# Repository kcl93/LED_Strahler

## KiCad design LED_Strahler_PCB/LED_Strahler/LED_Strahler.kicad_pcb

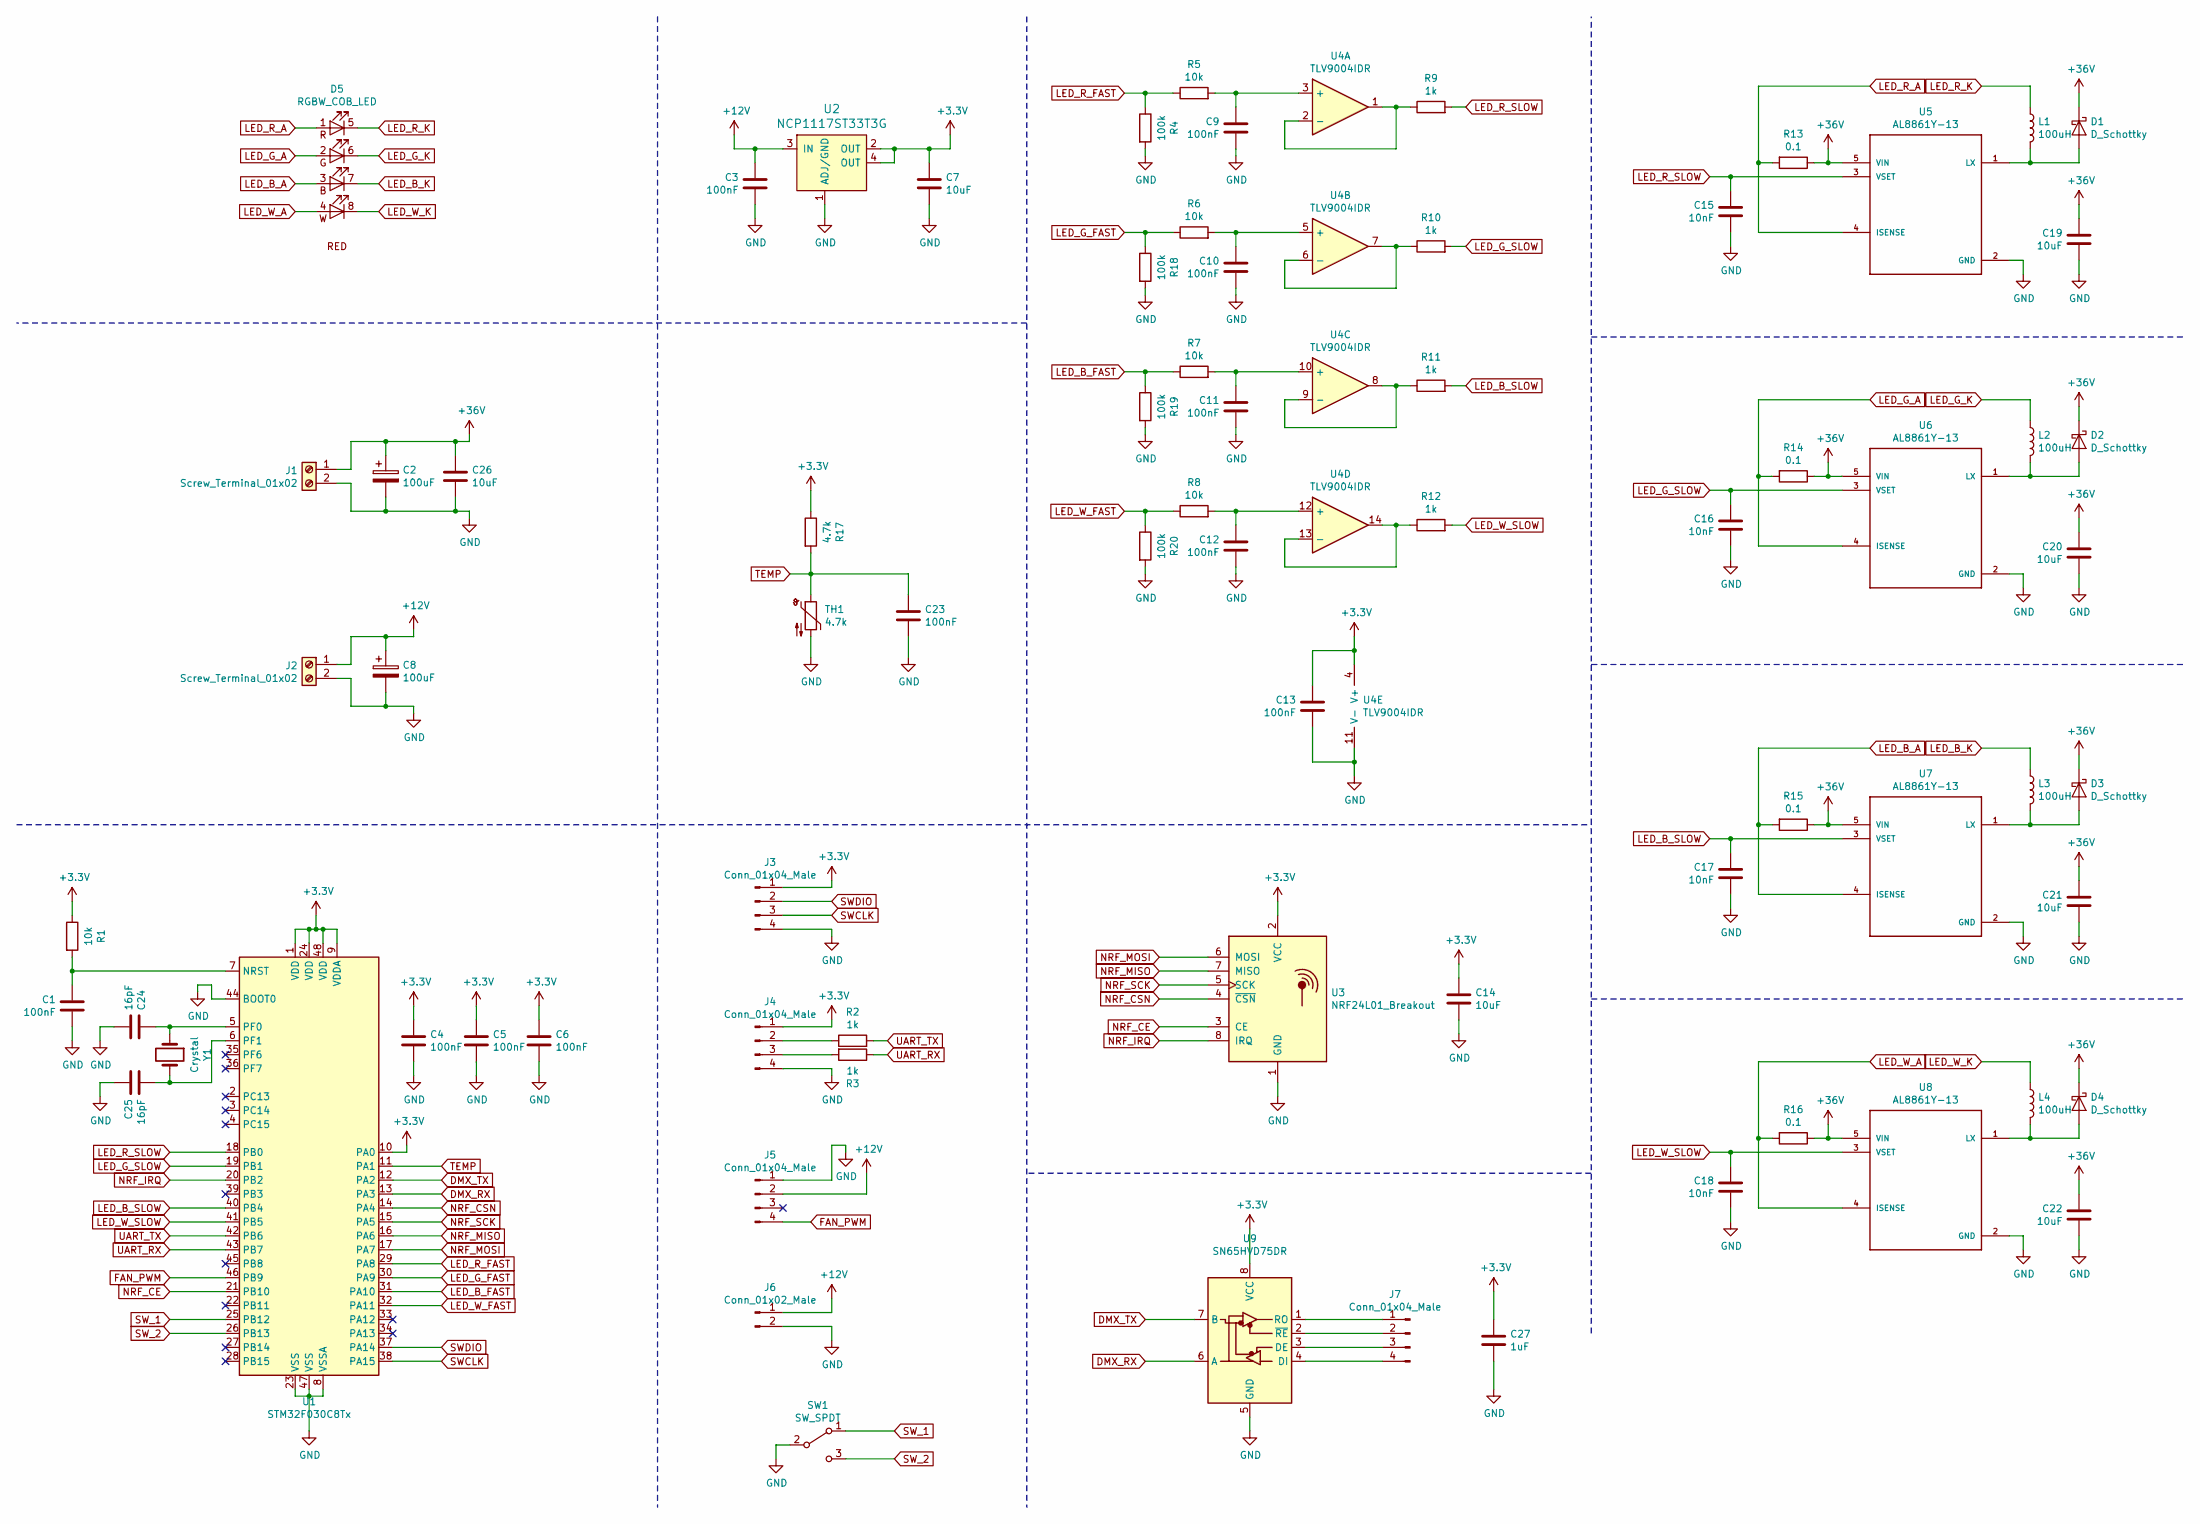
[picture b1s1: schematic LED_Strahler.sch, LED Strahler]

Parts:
C1, C3, C4, C5, C6, C9, C10, C11, C12, C13, C23: 100nF; C_0603_1608Metric_Pad1.05x0.95mm_HandSolder
C2, C8: 100uF; CP_Radial_D10.0mm_P5.00mm
C7, C14: 10uF; C_0805_2012Metric_Pad1.15x1.40mm_HandSolder
C15, C16, C17, C18: 10nF; C_0603_1608Metric_Pad1.05x0.95mm_HandSolder
C19, C20, C21, C22, C26: 10uF; C_1210_3225Metric_Pad1.42x2.65mm_HandSolder
C24, C25: 16pF; C_0603_1608Metric_Pad1.05x0.95mm_HandSolder
C27: 1uF; C_0805_2012Metric_Pad1.15x1.40mm_HandSolder
D1, D2, D3, D4: D_Schottky; D_SOD-123F
D5: RGBW_COB_LED; 50W_RGBW_COB_LED
J1, J2: Screw_Terminal_01x02; AMASS_XT30U-F_1x02_P5.0mm_Vertical
J3, J4, J7: Conn_01x04_Male; PinHeader_1x04_P2.54mm_Vertical
J5: Conn_01x04_Male; FanPinHeader_1x04_P2.54mm_Vertical
J6: Conn_01x02_Male; PinHeader_1x02_P2.54mm_Vertical
L1, L2, L3, L4: 100uH; L_Bourns_SRR1260
R1, R5, R6, R7, R8: 10k; R_0603_1608Metric_Pad1.05x0.95mm_HandSolder
R2, R3, R9, R10, R11, R12: 1k; R_0603_1608Metric_Pad1.05x0.95mm_HandSolder
R4, R18, R19, R20: 100k; R_0603_1608Metric_Pad1.05x0.95mm_HandSolder
R13, R14, R15, R16: 0.1; R_0805_2012Metric_Pad1.15x1.40mm_HandSolder
R17: 4.7k; R_0603_1608Metric_Pad1.05x0.95mm_HandSolder
SW1: SW_SPDT; SW_CuK_OS102011MA1QN1_SPDT_Angled
TH1: 4.7k; R_0603_1608Metric_Pad1.05x0.95mm_HandSolder
U1: STM32F030C8Tx; LQFP-48_7x7mm_P0.5mm
U2: NCP1117ST33T3G; SOT-223; MPN NCP1117ST33T3G; Digi-Key_PN NCP1117ST33T3GOSCT-ND
U3: NRF24L01_Breakout; nRF24L01_Breakout
U4: TLV9004IDR; SOIC-14_3.9x8.7mm_P1.27mm
U5, U6, U7, U8: AL8861Y-13; CONV_AL8861Y-13
U9: SN65HVD75DR; SOIC-8_3.9x4.9mm_P1.27mm
Y1: Crystal; Crystal_SMD_HC49-SD

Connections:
+3V3: C4.1, C5.1, C6.1, C7.1, C13.1, C14.1, C27.1, J3.1, J4.1, R1.1, R17.1, U1.1 (VDD), U1.9 (VDDA), U1.10 (PA0), U1.24 (VDD), U1.48 (VDD), U2.2 (OUT), U2.4 (OUT), U3.2 (VCC), U4.4 (V+), U9.8 (VCC)
+12V: C3.1, C8.1, J2.1, J5.2, J6.1, U2.3 (IN)
+36V: C2.1, C19.1, C20.1, C21.1, C22.1, C26.1, D1.1 (K), D2.1 (K), D3.1 (K), D4.1 (K), J1.1, R13.1, R14.1, R15.1, R16.1, U5.5 (VIN), U6.5 (VIN), U7.5 (VIN), U8.5 (VIN)
DMX_RX: U1.13 (PA3), U9.6 (A)
DMX_TX: U1.12 (PA2), U9.7 (B)
FAN_PWM: J5.4, U1.46 (PB9)
GND: C1.2, C2.2, C3.2, C4.2, C5.2, C6.2, C7.2, C8.2, C9.2, C10.2, C11.2, C12.2, C13.2, C14.2, C15.2, C16.2, C17.2, C18.2, C19.2, C20.2, C21.2, C22.2, C23.2, C24.2, C25.1, C26.2, C27.2, J1.2, J2.2, J3.4, J4.4, J5.1, J6.2, R4.2, R18.2, R19.2, R20.2, SW1.2 (B), TH1.2, U1.8 (VSSA), U1.23 (VSS), U1.44 (BOOT0), U1.47 (VSS), U2.1 (ADJ/GND), U3.1 (GND), U4.11 (V-), U5.2 (GND), U6.2 (GND), U7.2 (GND), U8.2 (GND), U9.5 (GND)
LED_B_A: D5.3 (A), R15.2, U7.4 (ISENSE)
LED_B_FAST: R7.1, R19.1, U1.31 (PA10)
LED_B_K: D5.7 (K), L3.1
LED_B_SLOW: C17.1, R11.2, U1.40 (PB4), U7.3 (VSET)
LED_G_A: D5.2 (A), R14.2, U6.4 (ISENSE)
LED_G_FAST: R6.1, R18.1, U1.30 (PA9)
LED_G_K: D5.6 (K), L2.1
LED_G_SLOW: C16.1, R10.2, U1.19 (PB1), U6.3 (VSET)
LED_R_A: D5.1 (A), R13.2, U5.4 (ISENSE)
LED_R_FAST: R4.1, R5.1, U1.29 (PA8)
LED_R_K: D5.5 (K), L1.1
LED_R_SLOW: C15.1, R9.2, U1.18 (PB0), U5.3 (VSET)
LED_W_A: D5.4 (A), R16.2, U8.4 (ISENSE)
LED_W_FAST: R8.1, R20.1, U1.32 (PA11)
LED_W_K: D5.8 (K), L4.1
LED_W_SLOW: C18.1, R12.2, U1.41 (PB5), U8.3 (VSET)
NRF_CE: U1.21 (PB10), U3.3 (CE)
NRF_CSN: U1.14 (PA4), U3.4 (~CSN)
NRF_IRQ: U1.20 (PB2), U3.8 (IRQ)
NRF_MISO: U1.16 (PA6), U3.7 (MISO)
NRF_MOSI: U1.17 (PA7), U3.6 (MOSI)
NRF_SCK: U1.15 (PA5), U3.5 (SCK)
unnamed: C1.1, R1.2, U1.7 (NRST)
unnamed: C9.1, R5.2, U4.3 (+)
unnamed: C10.1, R6.2, U4.5 (+)
unnamed: C11.1, R7.2, U4.10 (+)
unnamed: C12.1, R8.2, U4.12 (+)
unnamed: C24.1, U1.5 (PF0), Y1.1
unnamed: C25.2, U1.6 (PF1), Y1.2
unnamed: D1.2 (A), L1.2, U5.1 (LX)
unnamed: D2.2 (A), L2.2, U6.1 (LX)
unnamed: D3.2 (A), L3.2, U7.1 (LX)
unnamed: D4.2 (A), L4.2, U8.1 (LX)
unnamed: J4.2, R2.1
unnamed: J4.3, R3.2
unnamed: J7.1, U9.1 (RO)
unnamed: J7.2, U9.2 (~RE)
unnamed: J7.3, U9.3 (DE)
unnamed: J7.4, U9.4 (DI)
unnamed: R9.1, U4.1, U4.2 (-)
unnamed: R10.1, U4.6 (-), U4.7
unnamed: R11.1, U4.8, U4.9 (-)
unnamed: R12.1, U4.13 (-), U4.14
SWCLK: J3.3, U1.38 (PA15)
SWDIO: J3.2, U1.37 (PA14)
SW_1: SW1.1 (A), U1.25 (PB12)
SW_2: SW1.3 (C), U1.26 (PB13)
TEMP: C23.1, R17.2, TH1.1, U1.11 (PA1)
UART_RX: R3.1, U1.43 (PB7)
UART_TX: R2.2, U1.42 (PB6)

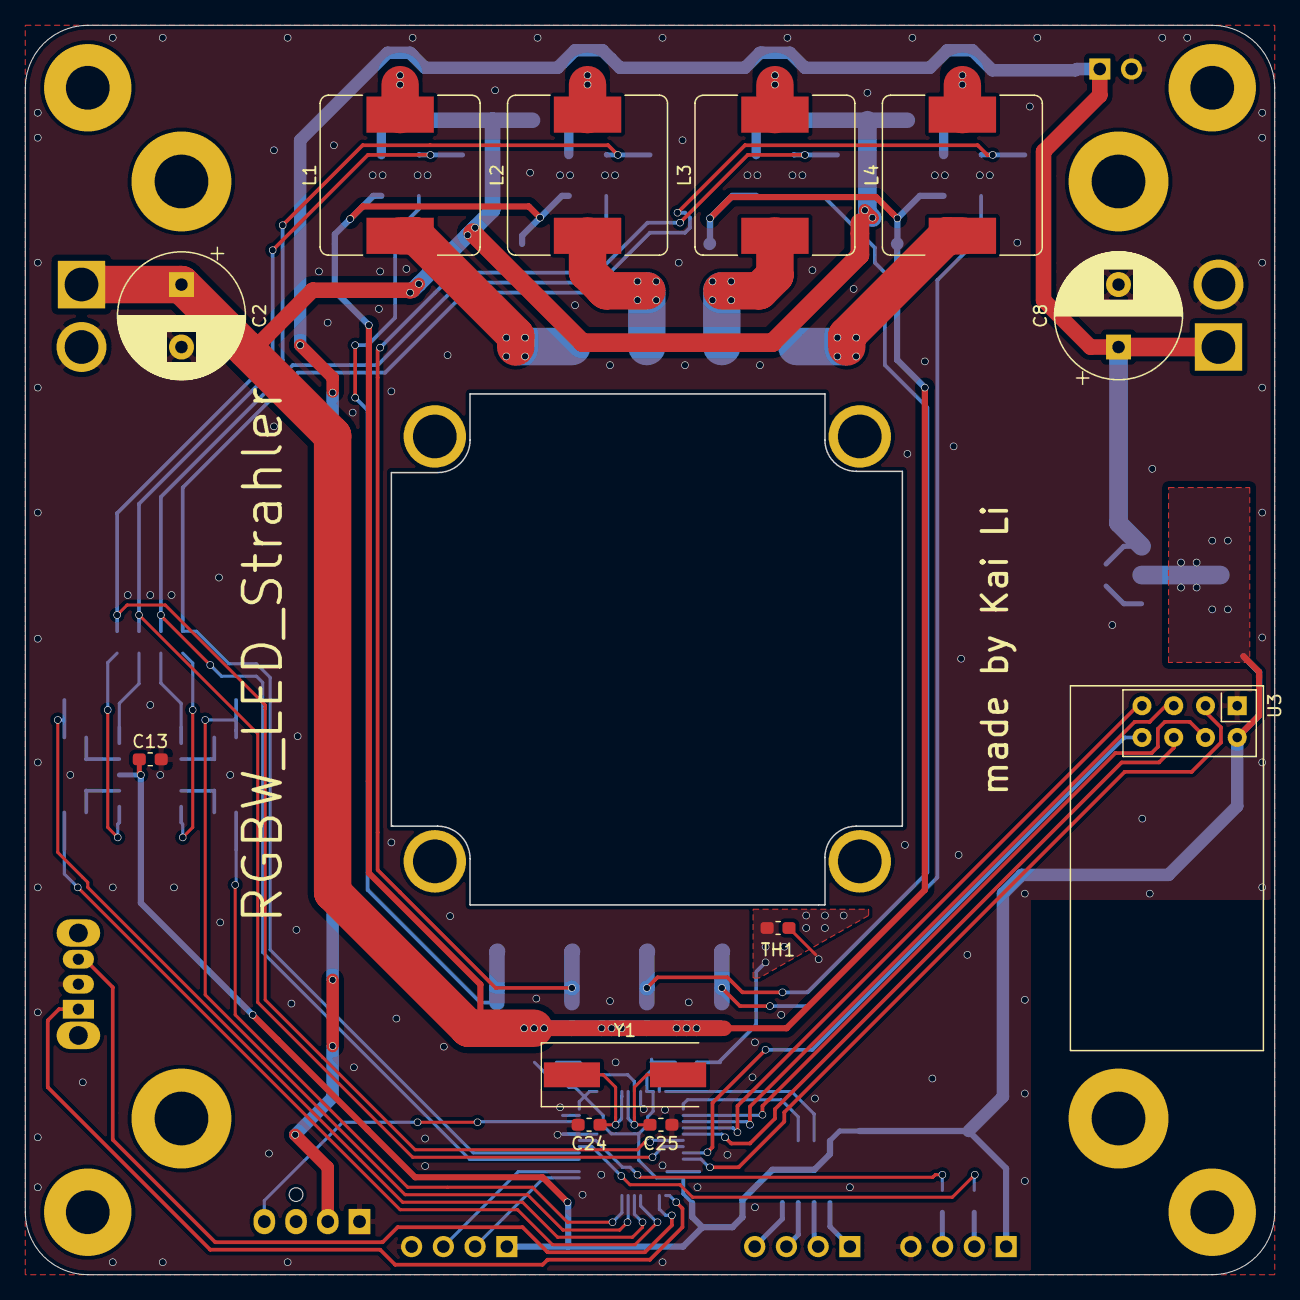
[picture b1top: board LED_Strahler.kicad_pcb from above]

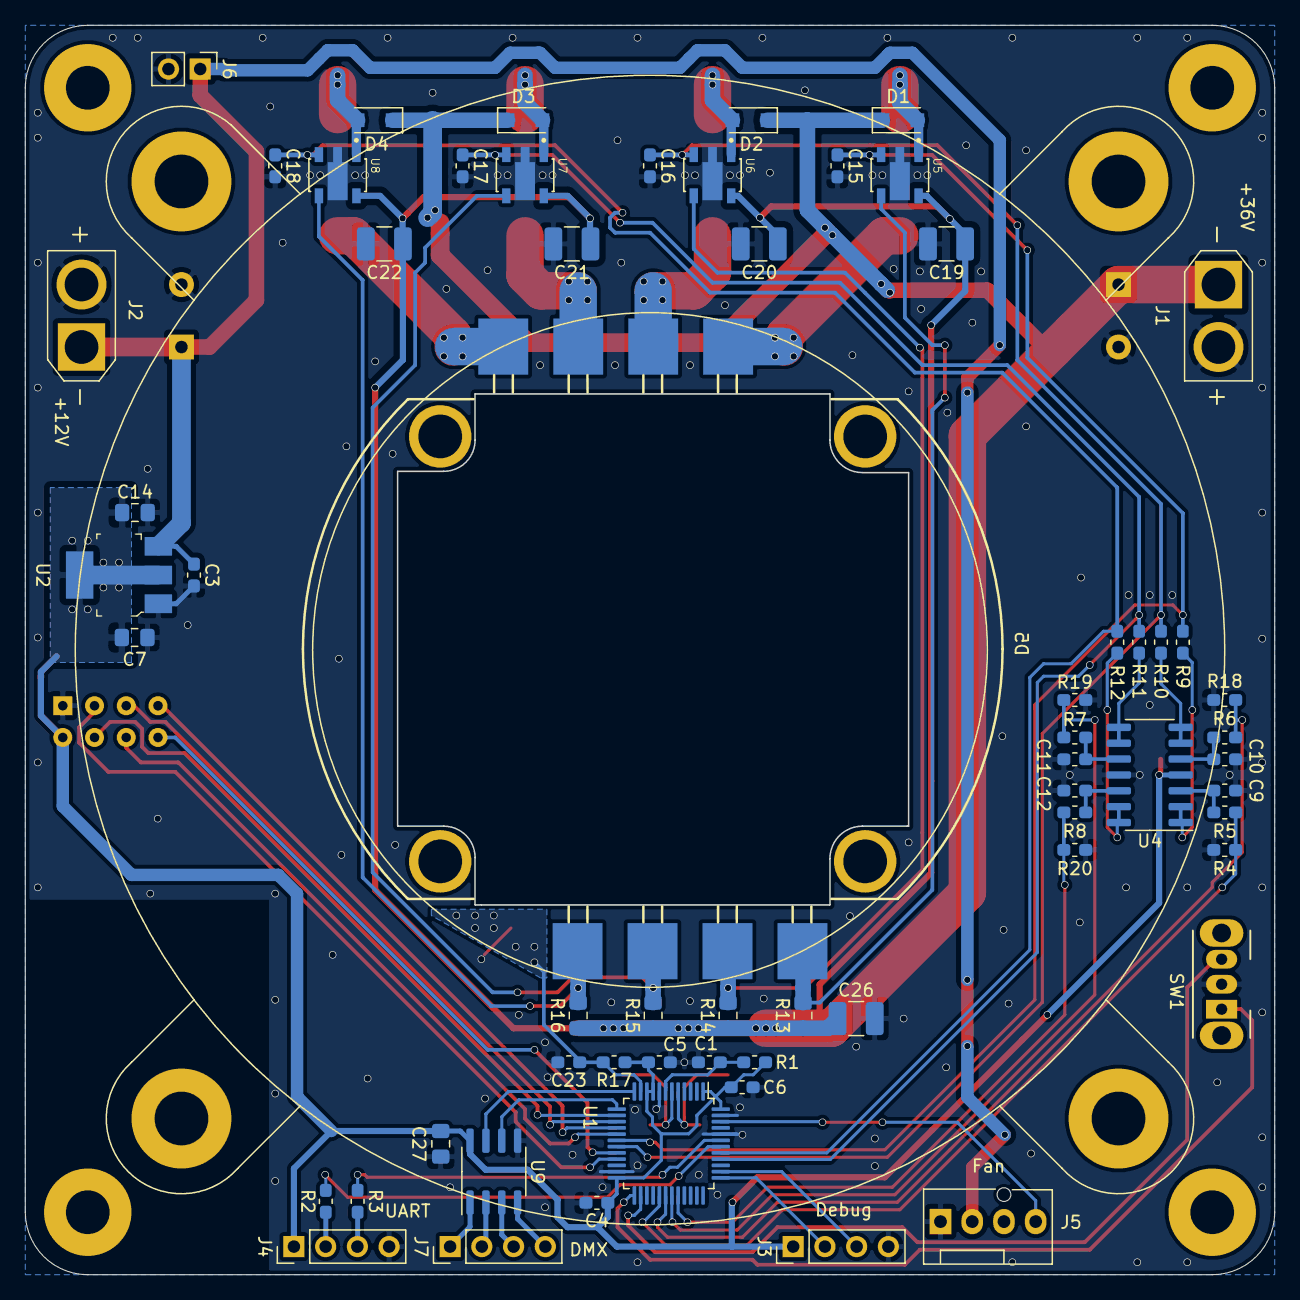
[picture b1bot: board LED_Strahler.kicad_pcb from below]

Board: 2 copper layers, 99.9 x 99.9 mm, 75 parts (62 on the bottom side), 57 nets.

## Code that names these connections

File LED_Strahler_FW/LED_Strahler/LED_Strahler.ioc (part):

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Mcu.Name=STM32F030C8Tx
Mcu.Package=LQFP48
Mcu.UserName=STM32F030C8Tx
PA1.GPIOParameters=GPIO_Label
PA1.GPIO_Label=TEMP
PA1.Mode=IN1
PA1.Signal=ADC_IN1
PA10.GPIOParameters=GPIO_ModeDefaultPP,GPIO_Speed,GPIO_Label
PA10.GPIO_Label=LED_B_FAST
PA10.GPIO_ModeDefaultPP=GPIO_MODE_AF_PP
PA10.GPIO_Speed=GPIO_SPEED_FREQ_HIGH
PA10.Signal=S_TIM1_CH3
PA11.GPIOParameters=GPIO_ModeDefaultPP,GPIO_Speed,GPIO_Label
PA11.GPIO_Label=LED_W_FAST
PA11.GPIO_ModeDefaultPP=GPIO_MODE_AF_PP
PA11.GPIO_Speed=GPIO_SPEED_FREQ_HIGH
PA11.Signal=S_TIM1_CH4
PA13.Mode=Serial_Wire
PA13.Signal=SYS_SWDIO
PA14.Mode=Serial_Wire
PA14.Signal=SYS_SWCLK
PA2.GPIOParameters=GPIO_Label
PA2.GPIO_Label=DMX_TX
PA2.Mode=Asynchronous
PA2.Signal=USART2_TX
PA3.GPIOParameters=GPIO_ModeDefaultPP,GPIO_PuPd,GPIO_Label
PA3.GPIO_Label=DMX_RX
PA3.GPIO_ModeDefaultPP=GPIO_MODE_AF_OD
PA3.GPIO_PuPd=GPIO_PULLUP
PA3.Mode=Asynchronous
PA3.Signal=USART2_RX
PA4.GPIOParameters=GPIO_Speed,PinState,GPIO_Label
PA4.GPIO_Label=NRF_CSN
PA4.GPIO_Speed=GPIO_SPEED_FREQ_MEDIUM
PA4.PinState=GPIO_PIN_SET
PA4.Signal=GPIO_Output
PA5.GPIOParameters=GPIO_Label
PA5.GPIO_Label=NRF_SCK
PA5.Mode=Full_Duplex_Master
PA5.Signal=SPI1_SCK
PA6.GPIOParameters=GPIO_Label
PA6.GPIO_Label=NRF_MISO
PA6.Mode=Full_Duplex_Master
PA6.Signal=SPI1_MISO
PA7.GPIOParameters=GPIO_Label
PA7.GPIO_Label=NRF_MOSI
PA7.Mode=Full_Duplex_Master
PA7.Signal=SPI1_MOSI
PA8.GPIOParameters=GPIO_ModeDefaultPP,GPIO_Speed,GPIO_Label
PA8.GPIO_Label=LED_R_FAST
PA8.GPIO_ModeDefaultPP=GPIO_MODE_AF_PP
PA8.GPIO_Speed=GPIO_SPEED_FREQ_HIGH
PA8.Signal=S_TIM1_CH1
PA9.GPIOParameters=GPIO_ModeDefaultPP,GPIO_Speed,GPIO_Label
PA9.GPIO_Label=LED_G_FAST
PA9.GPIO_ModeDefaultPP=GPIO_MODE_AF_PP
PA9.GPIO_Speed=GPIO_SPEED_FREQ_HIGH
PA9.Signal=S_TIM1_CH2
PB0.GPIOParameters=GPIO_ModeDefaultPP,GPIO_Speed,GPIO_Label
PB0.GPIO_Label=LED_R_SLOW
PB0.GPIO_ModeDefaultPP=GPIO_MODE_AF_OD
PB0.GPIO_Speed=GPIO_SPEED_FREQ_LOW
PB0.Signal=S_TIM3_CH3
PB1.GPIOParameters=GPIO_ModeDefaultPP,GPIO_Speed,GPIO_Label
PB1.GPIO_Label=LED_G_SLOW
PB1.GPIO_ModeDefaultPP=GPIO_MODE_AF_OD
PB1.GPIO_Speed=GPIO_SPEED_FREQ_LOW
PB1.Signal=S_TIM3_CH4
PB10.GPIOParameters=GPIO_Speed,GPIO_Label
PB10.GPIO_Label=NRF_CE
PB10.GPIO_Speed=GPIO_SPEED_FREQ_MEDIUM
PB10.Signal=GPIO_Output
PB12.GPIOParameters=GPIO_PuPd,GPIO_Label
PB12.GPIO_Label=SW_1
PB12.GPIO_PuPd=GPIO_PULLUP
PB12.Signal=GPIO_Input
PB13.GPIOParameters=GPIO_PuPd,GPIO_Label
PB13.GPIO_Label=SW_2
PB13.GPIO_PuPd=GPIO_PULLUP
PB13.Signal=GPIO_Input
PB2.GPIOParameters=GPIO_PuPd,GPIO_Label,GPIO_ModeDefaultEXTI
PB2.GPIO_Label=NRF_IRQ
PB2.GPIO_ModeDefaultEXTI=GPIO_MODE_IT_FALLING
PB2.GPIO_PuPd=GPIO_PULLUP
PB2.Signal=GPXTI2
PB4.GPIOParameters=GPIO_ModeDefaultPP,GPIO_Label
PB4.GPIO_Label=LED_B_SLOW
PB4.GPIO_ModeDefaultPP=GPIO_MODE_AF_OD
PB4.Signal=S_TIM3_CH1
PB5.GPIOParameters=GPIO_ModeDefaultPP,GPIO_Label
PB5.GPIO_Label=LED_W_SLOW
PB5.GPIO_ModeDefaultPP=GPIO_MODE_AF_OD
PB5.Signal=S_TIM3_CH2
PB6.GPIOParameters=GPIO_Label
PB6.GPIO_Label=UART_TX
PB6.Mode=Asynchronous
PB6.Signal=USART1_TX
PB7.GPIOParameters=GPIO_ModeDefaultPP,GPIO_PuPd,GPIO_Label
PB7.GPIO_Label=UART_RX
PB7.GPIO_ModeDefaultPP=GPIO_MODE_AF_OD
PB7.GPIO_PuPd=GPIO_PULLUP
PB7.Mode=Asynchronous
PB7.Signal=USART1_RX
PB9.GPIOParameters=GPIO_Speed,GPIO_PuPd,GPIO_Label
PB9.GPIO_Label=FAN_PWM
PB9.GPIO_PuPd=GPIO_PULLUP
PB9.GPIO_Speed=GPIO_SPEED_FREQ_MEDIUM
PB9.Signal=S_TIM17_CH1
PF0-OSC_IN.GPIOParameters=GPIO_Label
PF0-OSC_IN.GPIO_Label=OSC_IN
PF0-OSC_IN.Mode=HSE-External-Oscillator
PF0-OSC_IN.Signal=RCC_OSC_IN
PF1-OSC_OUT.GPIOParameters=GPIO_Label
PF1-OSC_OUT.GPIO_Label=OSC_OUT
PF1-OSC_OUT.Mode=HSE-External-Oscillator
PF1-OSC_OUT.Signal=RCC_OSC_OUT
RCC.SYSCLKFreq_VALUE=48000000
RCC.SYSCLKSource=RCC_SYSCLKSOURCE_PLLCLK
board=custom

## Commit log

2020-01-12 Create RGBW_Strahler_FW
2020-01-12 Updated FAN startup.
2020-01-12 Updated WIN tool.
2020-01-13 Got RF-link working!
2020-01-14 Updated WIN app to use a color picker.
2020-01-14 Added License
2020-01-15 Win app update.
2020-01-16 Scale colors to ushort
2020-01-16 Scale color sliders to ushort
2020-01-16 Updated WIN app.
2020-01-17 Win App Update
2020-01-18 First running base version.
2020-01-20 Improved MVVM conformity
2020-01-22 Add 3D models for case
2020-01-22 Various fixes
2020-01-30 Various fixes & improvements
2020-02-01 Fixed ping and getTemp. Repo cleanup.
2020-02-02 Fixed read temp. Various fixes and improvements.
2020-02-05 Improved LED fading
2020-03-29 Fixed PWM to have a linear duty cycle.
2020-04-06 Added option to set individual LED strahler only. Did some more prework for music and LJ control in the windows app.
2020-04-13 Added LJ mode to Win App
